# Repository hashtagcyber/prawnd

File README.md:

# Prawnd

An ESP32-based, Plaud-style voice recorder. Press a button to start/stop recording;
the device captures 16 kHz stereo audio to an SD card and POSTs each finished WAV
to a webserver you configure on-device.

- **Hardware** — Seeed XIAO ESP32C6, 2× INMP441 I²S mics (stereo), SPI microSD adapter, push-button. Wiring diagrams live in [`hardware/wiring.md`](hardware/wiring.md).
- **Firmware** — Arduino-ESP32 via PlatformIO. Source in [`firmware/`](firmware/).
- **Webservice** — Node.js + Fastify, SQLite-indexed, Dockerized. Source in [`server/`](server/).

> [!CAUTION]
> ## 🔓 HTTPS uploads use `setInsecure()` — TLS certificate validation is OFF
>
> When the configured Upload URL is `https://…`, the firmware uploads with
> `WiFiClientSecure::setInsecure()` (`firmware/src/uploader.cpp`), which **does
> the TLS handshake but does NOT validate the server's certificate**. The
> connection is encrypted, but there is **no protection against a
> man-in-the-middle**: anyone who can intercept the device's traffic can present
> a forged certificate, decrypt the upload, and **steal the API key** (which the
> device sends as `Authorization: Bearer …`).
>
> This is a **beta convenience only.** Before any non-hobby/production use, pin a
> CA bundle (e.g. ISRG Root X1) via `setCACert()` and remove `setInsecure()`, and
> treat each device's API key as compromised if its network is ever untrusted.
> Rotate keys in the web UI if in doubt.

## Quick start

```bash
# 1. Bring the server up locally
cd server
cp .env.example .env            # then edit PRAWND_API_KEY
docker compose up -d --build
curl -s http://localhost:8080/healthz   # {"ok":true}

# 2. Build the firmware
cd ../firmware
pio run                                  # first run downloads toolchains (slow)

# 3. Flash it (with the XIAO plugged in via USB-C)
pio run -t upload
pio device monitor                       # 115200 baud
```

On first boot the device has no WiFi configured, so it brings up an AP named
**`Prawnd-XXXX`** (password `prawnd1234`). Connect, browse to `http://192.168.4.1`,
fill in WiFi creds + upload URL + API key, hit save. The device reboots into STA
mode and is ready to record.

## Server

### Prereqs
- Docker / Docker Compose (Rancher Desktop, OrbStack, or Docker Desktop all fine)

### Build & run
```bash
cd server
cp .env.example .env       # set PRAWND_API_KEY
docker compose up -d --build
docker compose logs -f prawnd
```

The container exposes port `8080`, persists data under `./data/` on the host
(SQLite at `data/prawnd.sqlite`, WAVs under `data/audio/<device_id>/<yyyy>/<mm>/`).

### Browser UI

Visit `http://localhost:8080/` for a built-in single-page UI: enter your API key
once (cached in `localStorage`), filter by device id, and play back any recording
inline. Audio elements stream from `/recordings/:id/file?api_key=...` directly.
**Caveat**: the API key ends up in `<audio src>` attributes, so treat the URL as
secret on the LAN — don't share screenshots of the DOM.

### Endpoints

| Method | Path | Auth | Purpose |
|---|---|---|---|
| `GET`  | `/` | no | Built-in HTML UI. |
| `POST` | `/upload` | yes | Upload a WAV body. Headers: `Authorization: Bearer <key>` (or `X-API-Key: <key>`), `Content-Type: audio/wav`, `X-Device-Id: <id>`, `X-Client-Timestamp: <ms>` (optional). |
| `GET`  | `/recordings?limit=&cursor=&device_id=` | yes | Cursor-paginated list, newest first. |
| `GET`  | `/recordings/:id` | yes | JSON metadata. |
| `GET`  | `/recordings/:id/file` | yes | Raw `audio/wav` download. Auth accepts `?api_key=` query for `<audio>` playback. |
| `GET`  | `/healthz` | no | Liveness. |

API key auth accepts any of: `Authorization: Bearer <key>` header, `X-API-Key: <key>` header, or `?api_key=<key>` query param.

### Manual upload (smoke test without firmware)
```bash
curl -fsS -X POST \
  -H "Authorization: Bearer $PRAWND_API_KEY" \
  -H "Content-Type: audio/wav" \
  -H "X-Device-Id: bench" \
  --data-binary @some.wav \
  http://localhost:8080/upload
curl -fsS -H "Authorization: Bearer $PRAWND_API_KEY" http://localhost:8080/recordings | jq
```

### Stop / clean
```bash
docker compose down            # stop
rm -rf data && mkdir data      # wipe all recordings + db
```

## Firmware

### Prereqs
- [PlatformIO Core](https://platformio.org/install/cli) (`brew install platformio` on macOS)
- A USB-C cable that carries data
- A microSD card formatted **FAT32**

### Build
```bash
cd firmware
pio run
```
First run pulls the `espressif32` platform, the Arduino-ESP32 framework, the
toolchain, and the listed libs — expect several minutes on a fresh machine.
Subsequent builds take seconds. The flashable binary lands at
`.pio/build/xiao_esp32c6/firmware.bin`.

### Flash
Plug the XIAO in via USB-C. The C6 enters bootloader automatically on most
ports; if not, hold the **BOOT** button, tap **RESET**, then release BOOT.

The compiled artifact is `.pio/build/xiao_esp32c6/firmware.bin` (~1.1 MB).
```bash
pio run -t upload                # build + flash
pio run -t upload -t monitor     # flash + open serial monitor
```
Set the port explicitly if PlatformIO can't auto-detect:
```bash
pio run -t upload --upload-port /dev/cu.usbmodem<TAB>
```

### Serial monitor
```bash
pio device monitor               # 115200 baud (configured in platformio.ini)
```

### Optional: battery-monitoring addon

A second PlatformIO env, **`xiao_esp32c6_batt`**, compiles in an optional
MAX17048 LiPo fuel-gauge driver. The base `xiao_esp32c6` build is unchanged — the
addon is purely a compile-time flag (`-DENABLE_BATTERY`), so the standard
USB-powered firmware carries no battery code.

```bash
pio run -e xiao_esp32c6_batt              # build the battery variant
pio run -e xiao_esp32c6_batt -t upload    # build + flash it
```

Wire a MAX17048 breakout to the XIAO's I²C pins (`D4`=SDA, `D5`=SCL) and the BAT
pads — see [`hardware/wiring.md`](hardware/wiring.md#battery-fuel-gauge--max17048-optional-addon).
When a gauge is detected, `GET /status` gains `batt_pct` and `batt_mv` fields and
the config page shows the charge level; with no gauge fitted it reports
`battery: n/a` and behaves identically to the base firmware. The artifact lands
at `.pio/build/xiao_esp32c6_batt/firmware.bin`.

### First-time WiFi + upload setup
1. After flash, the device has no NVS config → it boots into AP mode.
2. From a phone or laptop, join the WiFi network **`Prawnd-XXXX`** (password `prawnd1234`, where `XXXX` is the last 4 hex of the MAC).
3. Open `http://192.168.4.1`.
4. Enter:
   - WiFi SSID + password (your home/office WiFi)
   - Upload URL — either:
     - **Local server:** `http://<your-mac-IP>:8080/upload` (plain HTTP), or
     - **Hosted beta:** `https://prawnd.dev.cobl.io/upload` (HTTPS — see the
       certificate-validation caution at the top of this README).
   - API key:
     - Local server: must match the server's `PRAWND_API_KEY`.
     - Hosted beta: log in at `https://prawnd.dev.cobl.io` with cobl.io and
       generate an **upload key** under *API keys*.
   - Device id (optional; auto-derived from MAC)
5. Hit **Save and reboot**. The device reconnects in STA mode.

To find the device's IP after reboot, watch the serial monitor or check your
router's DHCP list. `GET http://<device-ip>/status` returns its current state.

### Troubleshooting the first build

The `firmware/platformio.ini` deliberately uses the **pioarduino** platform fork
(`https://github.com/pioarduino/platform-espressif32/releases/...`) because the
official `platform-espressif32` still bundles Arduino-ESP32 v2.x, which has no
ESP32-C6 support. Two snags you may hit on a fresh machine:

- **`Could not find a version that satisfies the requirement cryptography` from pip** — your global pip is pointing at a local mirror that isn't serving. Override for the one command: `PIP_INDEX_URL=https://pypi.org/simple/ pio run`.
- **`FileNotFoundError: 'package-postinstall.py'` from the pioarduino esptool zip** — the v4.8.6 release omits the post-install script that PlatformIO tries to run. Stub it once: `touch ~/.platformio/packages/tool-esptoolpy/package-postinstall.py`, then re-run `pio run`.

### Recording flow
- **Short-press button** — start recording (LED on board lights, serial logs path)
- **Short-press again** — stop, patch WAV header, queue for upload, POST to server
- **Long-press ≥ 5 s** — factory reset (wipes NVS, reboots into AP mode)

Pending uploads (WiFi down, server unreachable) land in `/pending/` on the SD
card and retry once a minute while the device is idle and connected. Successfully
uploaded files move to `/uploaded/`.

## End-to-end verification

1. `cd server && docker compose up -d` — confirm `/healthz` returns 200.
2. `cd ../firmware && pio run -t upload && pio device monitor` — flash and watch boot logs.
3. Join the AP, configure with the upload URL pointing at your machine's LAN IP (NOT `localhost` — that's the device's own loopback).
4. Press the button, speak for a few seconds, press again.
5. Watch the serial log for `Upload .../ -> 200`.
6. `curl -fsS -H "Authorization: Bearer $PRAWND_API_KEY" http://localhost:8080/recordings | jq` — your recording shows up at the top.
7. Pull the file: `curl -fsS -H "Authorization: Bearer $PRAWND_API_KEY" http://localhost:8080/recordings/<id>/file -o out.wav` and play in VLC/Audacity — both L and R channels should be populated.

## Project layout

```
prawnd/
├── README.md
├── hardware.md                # high-level spec
├── hardware/
│   └── wiring.md              # per-device wiring diagrams + pin map
├── firmware/
│   ├── platformio.ini
│   ├── include/pins.h
│   └── src/                   # main, audio, wav, sd, wifi, portal, uploader, button, config,
│                              #   battery (optional MAX17048 addon, -DENABLE_BATTERY)
└── server/
    ├── Dockerfile
    ├── docker-compose.yml
    ├── package.json
    ├── .env.example
    └── src/                   # server.js, db.js, auth.js, wav.js,
                               #   routes/ (upload, recordings, health, ui)
```

## Hardware Links
I purchased the following parts on Amazon:
- https://a.co/d/0gR9T4nS
- https://a.co/d/04cU7Vte
- https://a.co/d/02JYXZO7
- https://a.co/d/06rkL2Dp

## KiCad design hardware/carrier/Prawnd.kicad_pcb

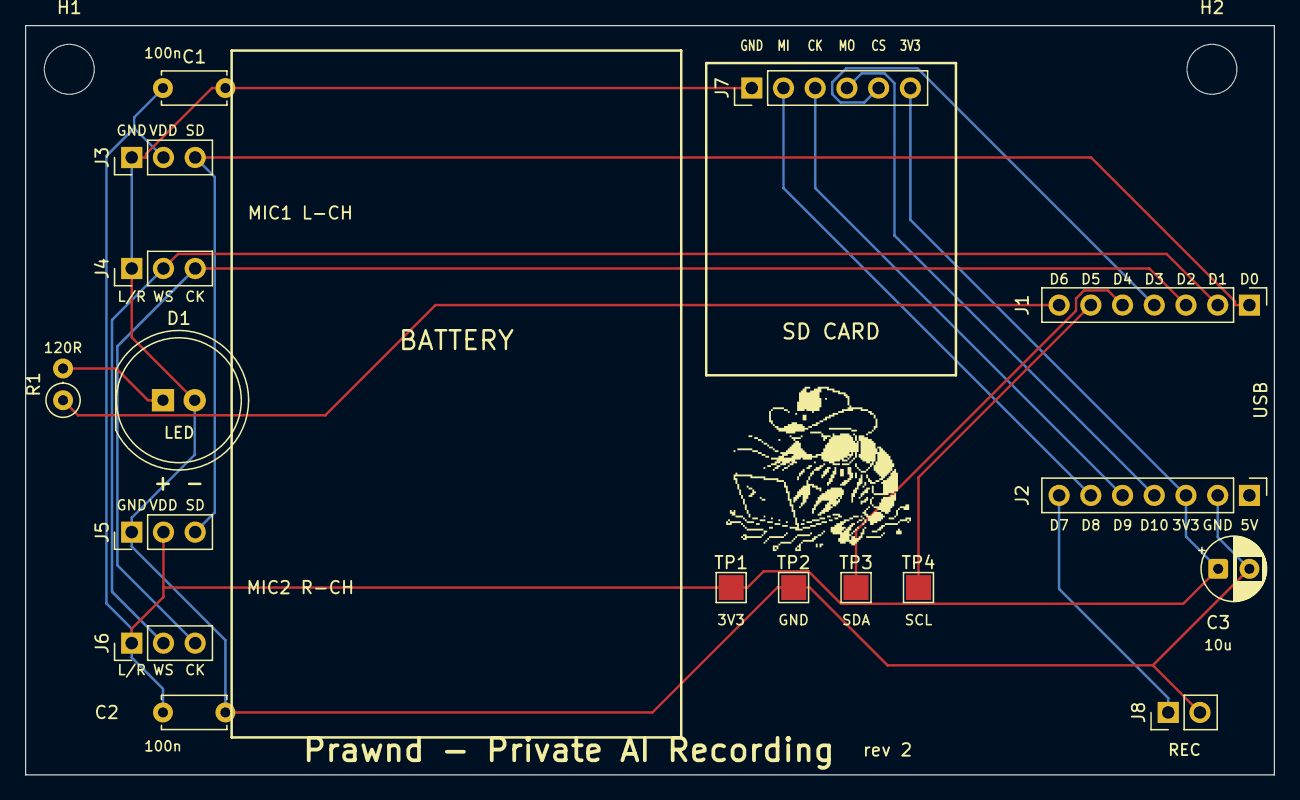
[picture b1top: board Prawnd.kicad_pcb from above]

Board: 2 copper layers, 100.0 x 60.0 mm, 19 parts (0 on the bottom side), 14 nets.

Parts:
C1, C2: 100n; C_Disc_D5.0mm_W2.5mm_P5.00mm
C3: 10u; CP_Radial_D5.0mm_P2.50mm
D1: LED_D10.0mm
H1, H2: Lanyard; MountingHole_4mm
J1: ESP32 L; PinHeader_1x07_P2.54mm_Vertical
J2: ESP32 R; PinHeader_1x07_P2.54mm_Vertical
J3: Mic1 R; PinHeader_1x03_P2.54mm_Vertical
J4: Mic1 L; PinHeader_1x03_P2.54mm_Vertical
J5: Mic2 R; PinHeader_1x03_P2.54mm_Vertical
J6: Mic2 L; PinHeader_1x03_P2.54mm_Vertical
J7: SD Card; PinHeader_1x06_P2.54mm_Vertical
J8: BTN; PinHeader_1x02_P2.54mm_Vertical
R1: 120R; R_Axial_DIN0207_L6.3mm_D2.5mm_P2.54mm_Vertical
TP1: +3V3; TestPoint_Pad_2.0x2.0mm
TP2: GND; TestPoint_Pad_2.0x2.0mm
TP3: SDA; TestPoint_Pad_2.0x2.0mm
TP4: SCL; TestPoint_Pad_2.0x2.0mm

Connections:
+3V3: C1.1, C2.1, C3.1, J2.3, J3.2, J5.2, J6.1, J7.6, TP1.1
BTN_D7: J2.7, J8.1
GND: C1.2, C2.2, C3.2, D1.LED-GND, J2.2, J3.1, J4.1, J5.1, J7.1, J8.2, TP2.1
I2C_SCL: J1.6, TP4.1
I2C_SDA: J1.5, TP3.1
I2S_BCLK: J1.3, J4.3, J6.3
I2S_SD: J1.1, J3.3, J5.3
I2S_WS: J1.2, J4.2, J6.2
LED_A: D1.LED-D6, R1.2
LED_D6: J1.7, R1.1
SD_CS: J1.4, J7.5
SD_MISO: J2.6, J7.2
SD_MOSI: J2.4, J7.4
SD_SCK: J2.5, J7.3

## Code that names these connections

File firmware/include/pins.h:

#pragma once
#include <Arduino.h>

// I2S (shared bus for both INMP441 mics)
constexpr int PIN_I2S_BCLK = 2;   // D2
constexpr int PIN_I2S_WS   = 1;   // D1
constexpr int PIN_I2S_DIN  = 0;   // D0

// SD card (SPI). SCK/MISO are swapped from the C6 defaults via the GPIO
// matrix: carrier rev 2 routes J7 crossing-free this way. (Rev 1 boards and
// the original point-to-point wiring used SCK=19/MISO=20.)
constexpr int PIN_SD_SCK   = 20;  // D9
constexpr int PIN_SD_MISO  = 19;  // D8
constexpr int PIN_SD_MOSI  = 18;  // D10
constexpr int PIN_SD_CS    = 21;  // D3

// Button (active-low with internal pull-up)
constexpr int PIN_BUTTON   = 17;  // D7

// Recording indicator LED (external, D6 -> series resistor -> LED -> GND).
// Driven HIGH while recording, LOW otherwise.
constexpr int PIN_REC_LED  = 16;  // D6

// Battery fuel gauge (optional addon — MAX17048 over I2C).
// Only used when the firmware is built with -DENABLE_BATTERY
// (the `xiao_esp32c6_batt` PlatformIO env). These are the XIAO's default
// I2C pins and are otherwise unused by the base firmware.
constexpr int PIN_BATT_SDA = 22;  // D4
constexpr int PIN_BATT_SCL = 23;  // D5

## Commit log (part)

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2026-06-11 stash
2026-06-14 add battery support and idea file
